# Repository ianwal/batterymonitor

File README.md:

<div align="center">

  Wi-Fi battery monitor using a custom [ESP32-C3](https://www.espressif.com/sites/default/files/documentation/esp32-c3-wroom-02_datasheet_en.pdf) board
  
</div>

---
## About:

I drive a Crown Victoria Police Interceptor. It is *old*. The only way I can tell if it has issues is through the instrument cluster.

When I don't drive for extended periods, the battery can drain to a harmful level. I needed an alert system for when the battery needs charging to avoid killing it (again, oops).

But, third-party battery monitor systems require a nearby Phone and Bluetooth. This is a problem.

#### Solution: Build my own!

## Hardware:
#### Features:
- GPIO screw terminal block with adjustable voltage divider
- [Low Iq LDO regulator](https://www.diodes.com/assets/Datasheets/AP7361C.pdf)
- [High accuracy temperature sensor](https://www.ti.com/lit/ds/symlink/tmp235-q1.pdf)
- USB-C
- Direct USB Serial/JTAG control without a USB to UART IC

The PCB was fabricated through [JLCPCB](https://jlcpcb.com/)
- JLCPCB's assembly service does not have the required components in their inventory. I assembled mine myself.

Components were ordered from [Mouser Electronics](https://www.mouser.com). You can find the complete bill of materials in the KiCad project.

## Software:
#### Features:
- Deep sleep to reduce power consumption

#### Setup:

Clone the repository and flash the microcontroller using the PlatformIO IDE Visual Studio Code extension.

Fill in your Home Assistant URL, Long Lived Access Token, Wi-Fi SSID, and Wi-Fi Password in `include/secrets.h`

#### Dependencies:
- [esp-ha-lib](https://github.com/ianwal/esp-ha-lib)
- FreeRTOS

You can modify the program to use a web server other than [Home Assistant](https://www.home-assistant.io/) easily. I use it for other IOT devices, so it was useful to incorporate into this project.

## Performance:

Voltage accuracy is around ± 0.1 V

Power consumption is still being evaluated

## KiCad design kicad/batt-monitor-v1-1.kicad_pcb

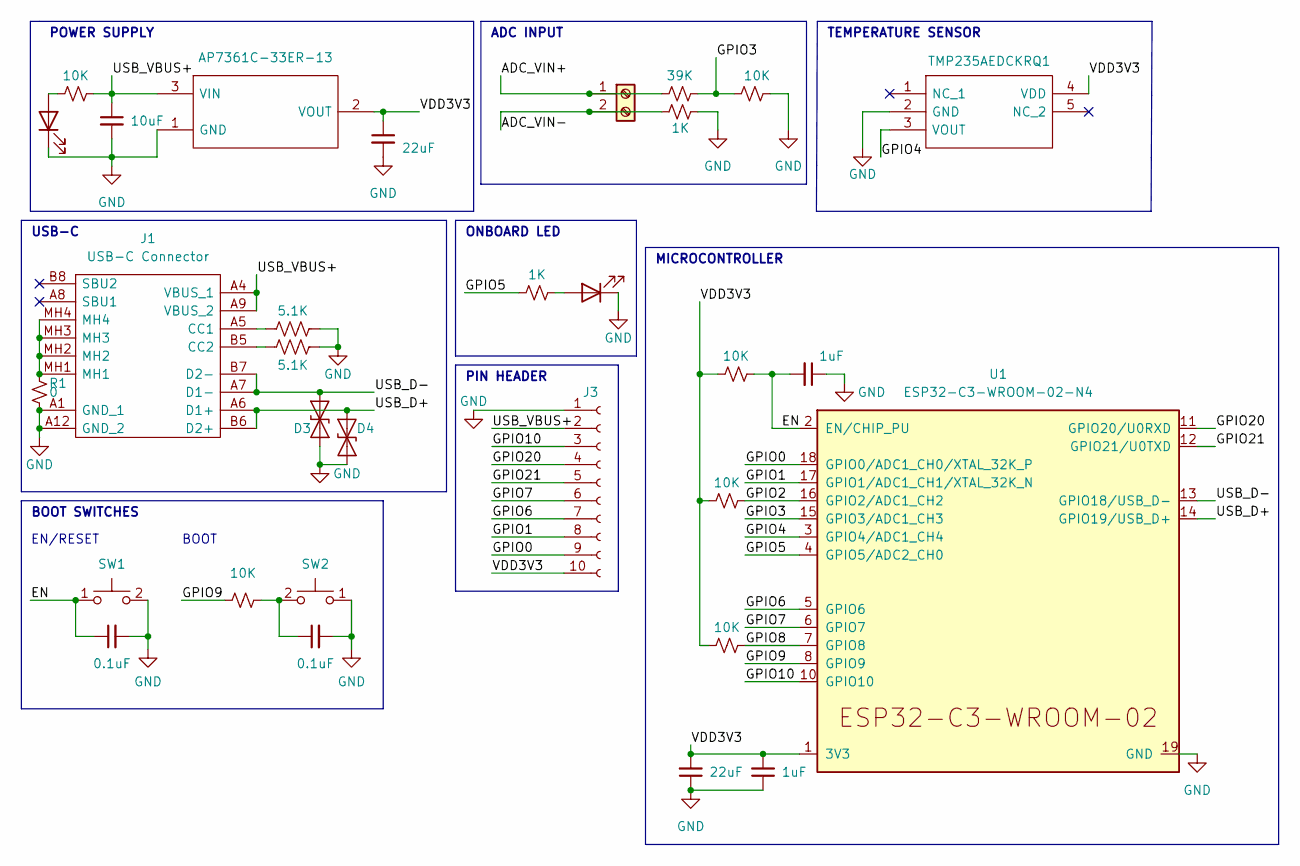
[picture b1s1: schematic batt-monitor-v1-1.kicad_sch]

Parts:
C1: 10uF; C_0603_1608Metric; LCSC C15849
C2, C3: 0.1uF; C_0603_1608Metric; LCSC C15849
C4, C5: 22uF; C_0603_1608Metric; LCSC C59461
C6, C7: 1uF; C_0603_1608Metric; LCSC C15849
D1, D2: LED; LED_0603_1608Metric; Mouser 710-150060RS75000
D3, D4: ESD9B5.0ST5G; D_SOD-923
IC1: AP7361C-33ER-13; SOT230P700X180-4N; Manufacturer_Part_Number AP7361C-33ER-13; Mouser Part Number 621-AP7361C-33ER-13
IC2: TMP235AEDCKRQ1; SOT65P210X110-5N; Manufacturer_Part_Number TMP235AEDCKRQ1; Mouser Part Number 595-TMP235AEDCKRQ1
J1: USB-C Connector; 2169900002; Manufacturer_Part_Number 2169900002
J2: Screw_Terminal_01x02; TB00250002BE; LCSC C8475
J3: Conn_01x10_Female; PinHeader_1x10_P2.54mm_Vertical
R1: 0; R_0603_1608Metric
R2, R3, R11, R12, R13, R14: 10K; R_0603_1608Metric; LCSC C25197
R4: 5.1K; R_0603_1608Metric; LCSC C23193
R5: 5.1K; R_0603_1608Metric
R6: 1K; R_0603_1608Metric
R9: 39K; R_0603_1608Metric; LCSC C23151
R10: 1K; R_0603_1608Metric; LCSC C22775
SW1, SW2: SW_Push; SW_SPST_TL3305A; Mouser 612-TL3305AF260QG
U1: ESP32-C3-WROOM-02-N4; ESP32-C3-WROOM-02

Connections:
/ADC_VIN+: J2.1, R9.1
/ADC_VIN-: J2.2, R10.1
/EN: C2.1, C7.2, R14.2, SW1.1, U1.2 (EN/CHIP_PU); also elsewhere on the board
/GPIO0: J3.9, U1.18 (GPIO0/ADC1_CH0/XTAL_32K_P)
/GPIO1: J3.8, U1.17 (GPIO1/ADC1_CH1/XTAL_32K_N)
/GPIO2: R12.2, U1.16 (GPIO2/ADC1_CH2)
/GPIO3: R9.2, R11.1, U1.15 (GPIO3/ADC1_CH3)
/GPIO4: IC2.3 (VOUT), U1.3 (GPIO4/ADC1_CH4)
/GPIO5: R6.1, U1.4 (GPIO5/ADC2_CH0)
/GPIO6: J3.7, U1.5 (GPIO6)
/GPIO7: J3.6, U1.6 (GPIO7)
/GPIO8: R13.2, U1.7 (GPIO8)
/GPIO9: R3.1, U1.8 (GPIO9)
/GPIO10: J3.3, U1.10 (GPIO10)
/GPIO20: J3.4, U1.11 (GPIO20/U0RXD)
/GPIO21: J3.5, U1.12 (GPIO21/U0TXD)
/USB_D+: D4.2 (A2), J1.A6 (D1+), J1.B6 (D2+), U1.14 (GPIO19/USB_D+)
/USB_D-: D3.2 (A2), J1.A7 (D1-), J1.B7 (D2-), U1.13 (GPIO18/USB_D-)
/USB_VBUS+: C1.1, IC1.3 (VIN), J1.A4 (VBUS_1), J1.A9 (VBUS_2), J3.2, R2.2
/VDD3V3: C4.1, C5.2, C6.2, IC1.2 (VOUT), IC2.4 (VDD), J3.10, R12.1, R13.1, R14.1, U1.1 (3V3)
GND: C1.2, C2.2, C3.2, C4.2, C5.1, C6.1, C7.1, D1.1 (K), D2.1 (K), D3.1 (A1), D4.1 (A1), IC1.1 (GND), IC2.2 (GND), J1.A1 (GND_1), J1.A12 (GND_2), J3.1, R1.2, R4.2, R5.2, R10.2, R11.2, SW1.2, SW2.1, U1.9 (GND), U1.19 (GND); also elsewhere on the board
unnamed 21: C3.1, R3.2, SW2.2; also elsewhere on the board
unnamed: D1.2 (A), R2.1
unnamed: D2.2 (A), R6.2
unnamed: J1.A5 (CC1), R4.1
unnamed: J1.B5 (CC2), R5.1
unnamed: J1.MH1, J1.MH2, J1.MH3, J1.MH4, R1.1

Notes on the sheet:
ONBOARD LED
ADC INPUT
BOOT
MICROCONTROLLER
EN/RESET
USB-C
BOOT SWITCHES
POWER SUPPLY
TEMPERATURE SENSOR
PIN HEADER

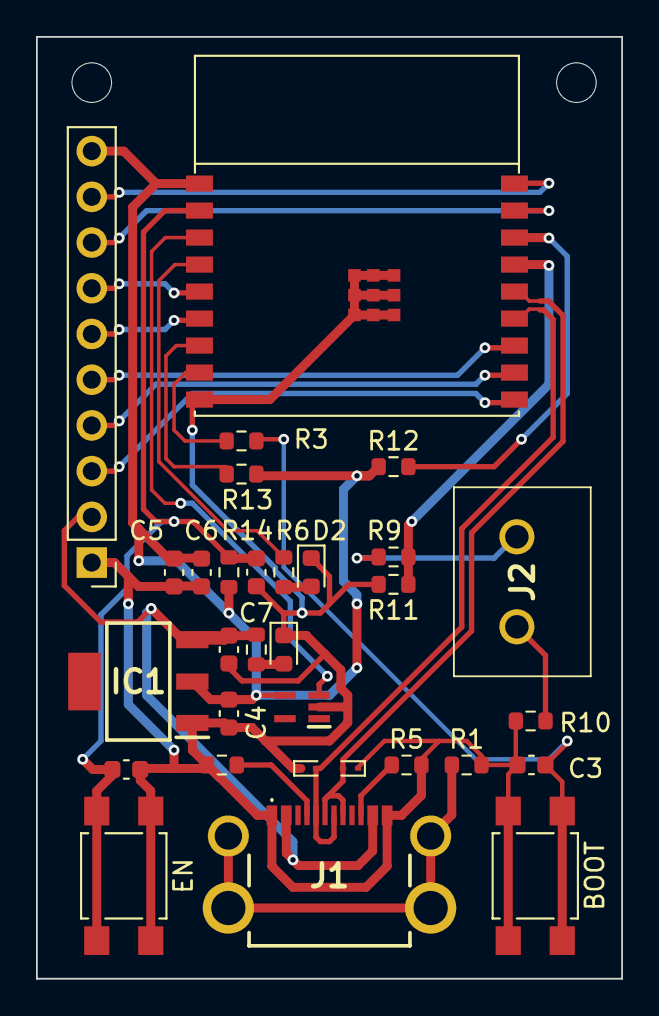
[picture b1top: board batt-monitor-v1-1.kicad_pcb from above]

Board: 2 copper layers, 32.5 x 52.3 mm, 31 parts (0 on the bottom side), 27 nets.

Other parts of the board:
BOOT: SW_Push; SW_SPST_TL3305A
EN: SW_Push; SW_SPST_TL3305A

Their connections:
/EN: EN.1; also elsewhere on the board
GND: BOOT.1, EN.2; also elsewhere on the board
unnamed 21: BOOT.2; also elsewhere on the board

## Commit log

2023-05-20 Initial upload from old repo
2023-05-24 Added ESP32C3 support
    - Also fixed wrong function name from new esp-ha-lib update
2023-05-24 Moved adc battery read logic to separate function
2023-06-04 Update function name from esp-ha-lib
    Also added a check for null get_entity in sensor_upload test
2023-06-04 Add Battery TAG name for logging
2023-06-04 Add basic information and pictures
2023-06-04 Rename upload_battery, add wifi check before upload
2023-06-04 Move common config to [env]. Add color monitor.
2023-06-04 Decrease time not in deep sleep
    - Remove deep sleep timer since it's only used for debugging currently
    - Remove NVS init since only the timer needed it
    WiFi does NVS init in wifi_init_sta() for itself
2023-06-04 Add About section and fill out others
2023-06-06 Update ADC to new driver
    * See more information [here](https://docs.espressif.com/projects/esp-idf/en/v5.0.2/esp32s2/migration-guides/release-5.x/peripherals.html)
2023-06-10 Improve resilience to WiFi failure
    * Move WiFi startup and battery reading to tasks
    * Attempt upload multiple times before sleeping
    * Set default WiFi condition to disconnected
2023-06-10 Add support for line calibration
    Some older ESP32's don't support curve calibration.
2023-07-23 Add project wide vscode settings
2023-07-23 New formatting style
    Clang formatter, Linux brace style,
2023-07-23 Add esp-ha-lib submodule for testing
2023-07-23 Move entity alloc to battery, add missing headers
    Also move nvs init from wifi to main
2023-10-29 Move to CPP for esp-ha-lib
2024-02-17 Change gtest to Unity, add namespaces, convert wifi.c to cpp, fix compat. with newest version of esphalib, add utilities
2024-02-17 Cleanup
2024-02-17 Remove clang-format extension
2024-02-17 Change ESP32C3 bootloader optimization level to -O2, enable stack-smashing protection
2024-02-25 Remove NVS from test, enable Newlib nano
2024-02-25 Fix wifi mode, remove unused wifi function, set wifi to use RAM instead of flash
2024-02-25 Stop wifi before sleep
2024-02-25 Remove remnantst of NVS
2024-02-25 Cleanup battery module
2024-02-25 Fix wifi storage NVS setting
2024-02-25 Fix crashes in ADC battery after cleanup
2024-02-25 Use std::chrono literals for readability
